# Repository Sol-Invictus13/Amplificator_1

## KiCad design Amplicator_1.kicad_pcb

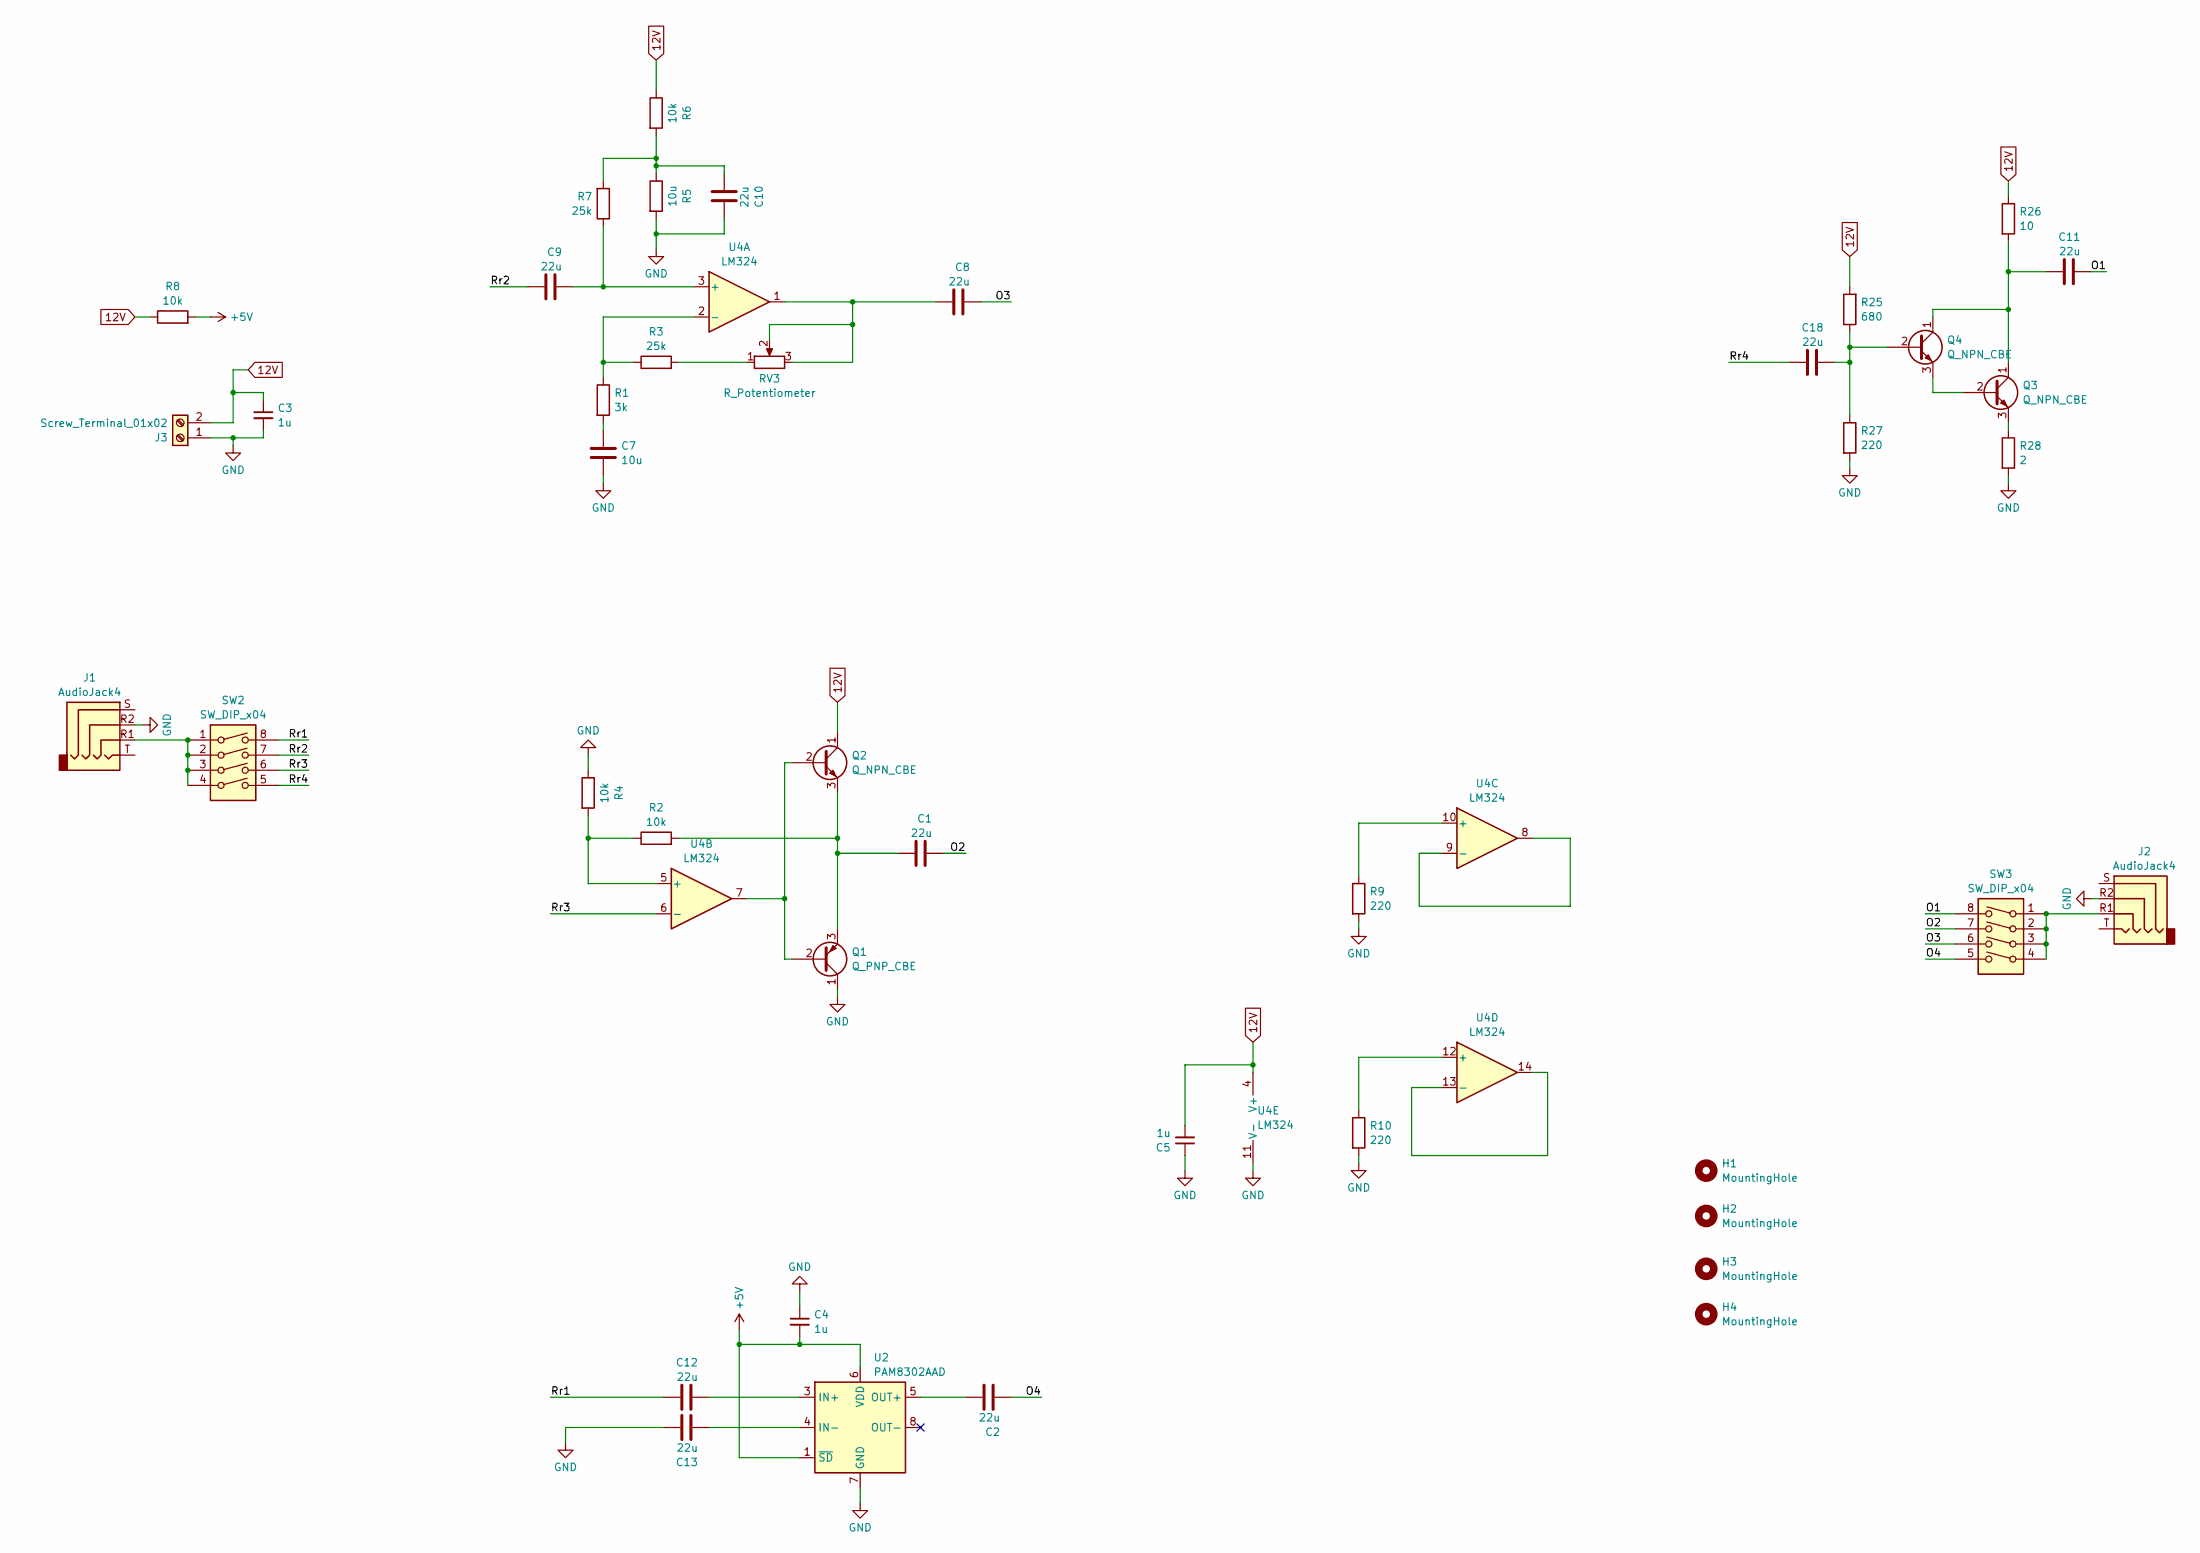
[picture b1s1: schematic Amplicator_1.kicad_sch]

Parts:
C1, C2, C8, C9, C10, C11, C12, C13, C18: 22u; CP_Radial_D5.0mm_P2.50mm
C3, C4, C5: 1u; C_Disc_D7.5mm_W2.5mm_P5.00mm
C7: 10u; CP_Radial_D5.0mm_P2.50mm
H1, H2, H3, H4: MountingHole; MountingHole_3.2mm_M3_DIN965
J1, J2: AudioJack4; Jack_3.5mm_KoreanHropartsElec_PJ-320D-4A_Horizontal
J3: Screw_Terminal_01x02; PhoenixContact_MC_1,5_2-G-5.08_1x02_P5.08mm_Horizontal
Q1: Q_PNP_CBE; TO-92_Inline_Wide
Q2, Q3, Q4: Q_NPN_CBE; TO-92_Inline_Wide
R1: 3k; R_Axial_DIN0204_L3.6mm_D1.6mm_P5.08mm_Horizontal
R2, R4, R6, R8: 10k; R_Axial_DIN0204_L3.6mm_D1.6mm_P5.08mm_Horizontal
R3, R7: 25k; R_Axial_DIN0204_L3.6mm_D1.6mm_P5.08mm_Horizontal
R5: 10u; R_Axial_DIN0204_L3.6mm_D1.6mm_P5.08mm_Horizontal
R9, R10, R27: 220; R_Axial_DIN0204_L3.6mm_D1.6mm_P5.08mm_Horizontal
R25: 680; R_Axial_DIN0204_L3.6mm_D1.6mm_P5.08mm_Horizontal
R26: 10; R_Axial_DIN0204_L3.6mm_D1.6mm_P5.08mm_Horizontal
R28: 2; R_Axial_DIN0204_L3.6mm_D1.6mm_P5.08mm_Horizontal
RV3: R_Potentiometer; Potentiometer_Bourns_3266Y_Vertical
SW2, SW3: SW_DIP_x04; SW_DIP_SPSTx04_Slide_9.78x12.34mm_W7.62mm_P2.54mm
U2: PAM8302AAD; SOIC-8_3.9x4.9mm_P1.27mm
U4: LM324; SOIC-14_3.9x8.7mm_P1.27mm

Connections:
12V: C3.1, C5.2, J3.2, Q2.1 (C), R6.1, R8.1, R25.2, R26.1, U4.4 (V+)
+5V: C4.2, R8.2, U2.1 (~SD), U2.6 (VDD)
/O1: C11.2, SW3.8
/O2: C1.2, SW3.7
/O3: C8.2, SW3.6
/O4: C2.2, SW3.5
/Rr1: C12.1, SW2.8
/Rr2: C9.1, SW2.7
/Rr3: SW2.6, U4.6 (-)
/Rr4: C18.1, SW2.5
GND: C3.2, C4.1, C5.1, C7.2, C10.2, C13.1, J1.R2, J2.R2, J3.1, Q1.1 (C), R4.1, R5.2, R9.2, R10.2, R27.2, R28.2, U2.7 (GND), U4.11 (V-)
unnamed: C7.1, R1.2
unnamed: C8.1, RV3.2, RV3.3, U4.1
unnamed: C10.1, R5.1, R6.2, R7.2
unnamed: J1.R1, SW2.1, SW2.2, SW2.3, SW2.4
unnamed: J2.R1, SW3.1, SW3.2, SW3.3, SW3.4
unnamed: Q1.2 (B), Q2.2 (B), U4.7
unnamed: C1.1, Q1.3 (E), Q2.3 (E), R2.2
unnamed: Q3.2 (B), Q4.3 (E)
unnamed: C11.1, Q3.1 (C), Q4.1 (C), R26.2
unnamed: Q3.3 (E), R28.1
unnamed: C18.2, Q4.2 (B), R25.1, R27.1
unnamed: R3.2, RV3.1
unnamed: C12.2, U2.3 (IN+)
unnamed: C13.2, U2.4 (IN-)
unnamed: C2.1, U2.5 (OUT+)
unnamed: C9.2, R7.1, U4.3 (+)
unnamed: R1.1, R3.1, U4.2 (-)
unnamed: R2.1, R4.2, U4.5 (+)
unnamed: R9.1, U4.10 (+)
unnamed: U4.8, U4.9 (-)
unnamed: R10.1, U4.12 (+)
unnamed: U4.13 (-), U4.14

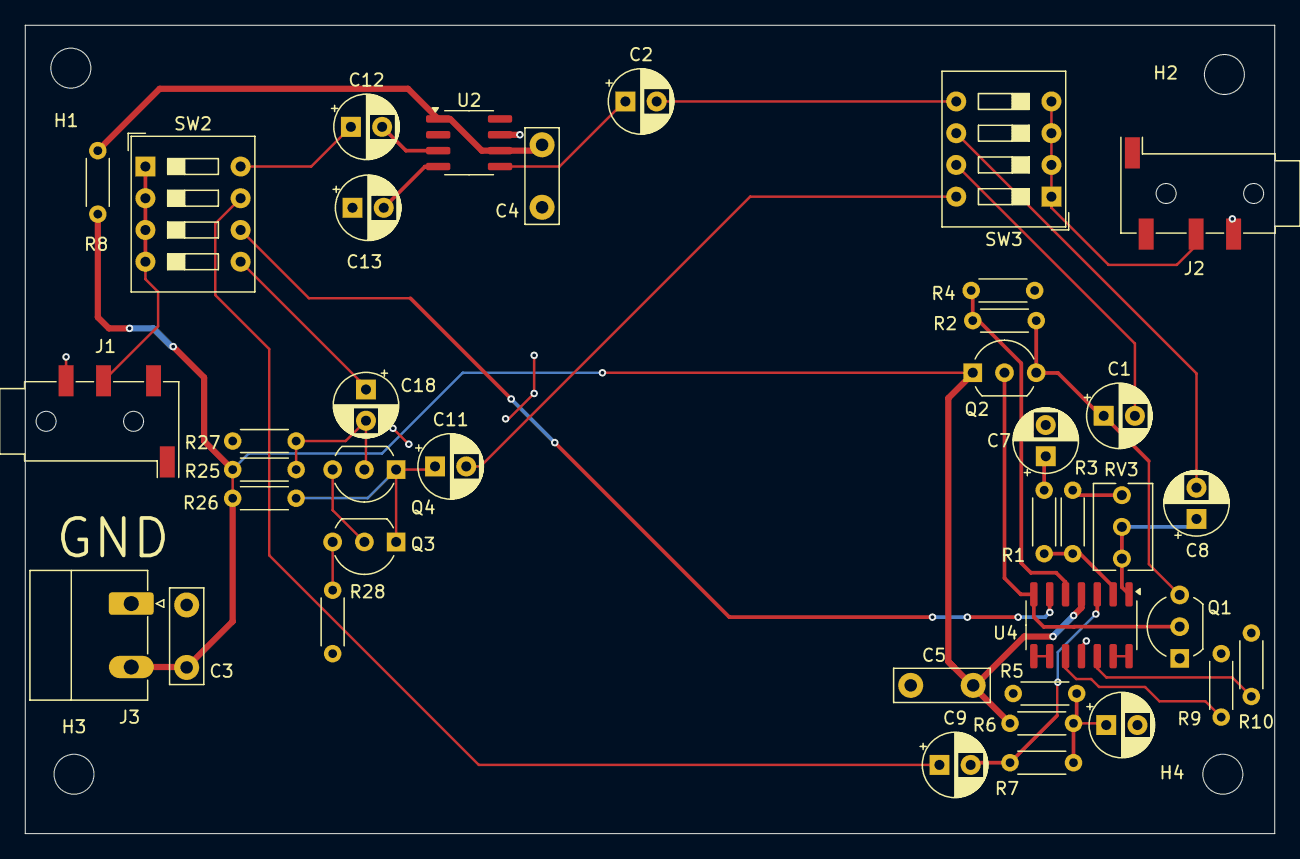
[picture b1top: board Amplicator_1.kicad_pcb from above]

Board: 2 copper layers, 100.0 x 64.7 mm, 43 parts (0 on the bottom side), 33 nets.

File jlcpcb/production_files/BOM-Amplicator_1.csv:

Comment,Designator,Footprint,LCSC
220,R10,R_Axial_DIN0204_L3.6mm_D1.6mm_P5.08mm_Horizontal,
220,R9,R_Axial_DIN0204_L3.6mm_D1.6mm_P5.08mm_Horizontal,
Screw_Terminal_01x02,J3,"PhoenixContact_MC_1,5_2-G-5.08_1x02_P5.08mm_Horizontal",
1u,C5,C_Disc_D7.5mm_W2.5mm_P5.00mm,
1u,C4,C_Disc_D7.5mm_W2.5mm_P5.00mm,
1u,C3,C_Disc_D7.5mm_W2.5mm_P5.00mm,
22u,C2,CP_Radial_D5.0mm_P2.50mm,
22u,C11,CP_Radial_D5.0mm_P2.50mm,
R_Potentiometer,RV3,Potentiometer_Bourns_3266Y_Vertical,
3k,R1,R_Axial_DIN0204_L3.6mm_D1.6mm_P5.08mm_Horizontal,
10,R26,R_Axial_DIN0204_L3.6mm_D1.6mm_P5.08mm_Horizontal,
22u,C8,CP_Radial_D5.0mm_P2.50mm,
10k,R2,R_Axial_DIN0204_L3.6mm_D1.6mm_P5.08mm_Horizontal,
10u,C7,CP_Radial_D5.0mm_P2.50mm,
Q_PNP_CBE,Q1,TO-92_Inline_Wide,
22u,C9,CP_Radial_D5.0mm_P2.50mm,
LM324,U4,SOIC-14_3.9x8.7mm_P1.27mm,
10k,R4,R_Axial_DIN0204_L3.6mm_D1.6mm_P5.08mm_Horizontal,
22u,C1,CP_Radial_D5.0mm_P2.50mm,
Q_NPN_CBE,Q4,TO-92_Inline_Wide,
SW_DIP_x04,SW3,SW_DIP_SPSTx04_Slide_9.78x12.34mm_W7.62mm_P2.54mm,
10k,R6,R_Axial_DIN0204_L3.6mm_D1.6mm_P5.08mm_Horizontal,
220,R27,R_Axial_DIN0204_L3.6mm_D1.6mm_P5.08mm_Horizontal,
Q_NPN_CBE,Q2,TO-92_Inline_Wide,
Q_NPN_CBE,Q3,TO-92_Inline_Wide,
680,R25,R_Axial_DIN0204_L3.6mm_D1.6mm_P5.08mm_Horizontal,
PAM8302AAD,U2,SOIC-8_3.9x4.9mm_P1.27mm,
SW_DIP_x04,SW2,SW_DIP_SPSTx04_Slide_9.78x12.34mm_W7.62mm_P2.54mm,
25k,R3,R_Axial_DIN0204_L3.6mm_D1.6mm_P5.08mm_Horizontal,
2,R28,R_Axial_DIN0204_L3.6mm_D1.6mm_P5.08mm_Horizontal,
AudioJack4,J1,Jack_3.5mm_KoreanHropartsElec_PJ-320D-4A_Horizontal,
10u,R5,R_Axial_DIN0204_L3.6mm_D1.6mm_P5.08mm_Horizontal,
22u,C13,CP_Radial_D5.0mm_P2.50mm,
22u,C10,CP_Radial_D5.0mm_P2.50mm,
AudioJack4,J2,Jack_3.5mm_KoreanHropartsElec_PJ-320D-4A_Horizontal,
22u,C18,CP_Radial_D5.0mm_P2.50mm,
10k,R8,R_Axial_DIN0204_L3.6mm_D1.6mm_P5.08mm_Horizontal,
25k,R7,R_Axial_DIN0204_L3.6mm_D1.6mm_P5.08mm_Horizontal,
22u,C12,CP_Radial_D5.0mm_P2.50mm,

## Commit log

2026-01-11 v2
    cleanup
2026-01-12 Create .gitignore
    Ignoring the backups folder in gitignore
